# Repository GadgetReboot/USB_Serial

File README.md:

# USB_Serial
3.3v/5v CH340 USB to UART interface with all flow control and indicator signals broken out

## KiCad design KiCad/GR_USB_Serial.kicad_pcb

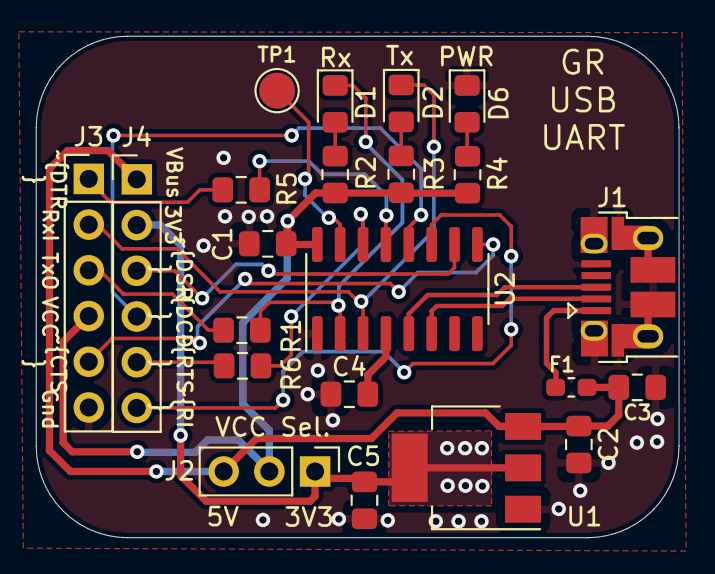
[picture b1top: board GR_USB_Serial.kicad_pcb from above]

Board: 2 copper layers, 35.7 x 27.9 mm, 22 parts (0 on the bottom side), 23 nets.

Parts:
C1, C2, C4: 100nF; C_0805_2012Metric_Pad1.15x1.40mm_HandSolder
C3: 1uF; C_0805_2012Metric_Pad1.15x1.40mm_HandSolder
C5: 4.7uF; C_0805_2012Metric_Pad1.15x1.40mm_HandSolder
D1: Rx; LED_0805_2012Metric_Pad1.15x1.40mm_HandSolder
D2: Tx; LED_0805_2012Metric_Pad1.15x1.40mm_HandSolder
D6: Power; LED_0805_2012Metric_Pad1.15x1.40mm_HandSolder
F1: MF-FSMF050X; R_0603_1608Metric_Pad1.05x0.95mm_HandSolder
J1: USB_B_Micro; USB_Micro-B_Amphenol_10103594-0001LF_Horizontal
J2: Conn_01x03; PinHeader_1x03_P2.54mm_Vertical
J3, J4: Conn_01x06; PinHeader_1x06_P2.54mm_Vertical
R1, R2, R3, R4, R5, R6: 1K; R_0805_2012Metric_Pad1.15x1.40mm_HandSolder
TP1: TestPoint; TestPoint_Pad_D2.0mm
U1: AMS1117-3.3; SOT-223-3_TabPin2
U2: CH340C; SOIC-16_3.9x9.9mm_P1.27mm

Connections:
+3V3: C5.1, J2.1, J4.2, U1.2
/RX_In: D2.1, J3.2, U2.3
/TX_Out: J3.3, R1.2
/~CTS: J3.5, U2.9
/~DCD: J4.4, U2.12
/~DSR: J4.3, U2.10
/~DTR: J3.1, R5.2
/~RI: J4.6, U2.11
/~RTS: J4.5, R6.2
GNDREF: C1.2, C2.2, C3.2, C4.2, C5.2, D6.1, J1.5, J1.6, J3.6, U1.1, U2.1
unnamed: C4.1, U2.4
unnamed: D1.1, R1.1, U2.2
unnamed: D1.2, R2.1
unnamed: D2.2, R3.1
unnamed: D6.2, R4.2
unnamed: F1.1, J1.1
unnamed: J1.2, U2.6
unnamed: J1.3, U2.5
unnamed: R5.1, U2.13
unnamed: R6.1, U2.14
unnamed: TP1.1, U2.15
VBUS: C2.1, C3.1, F1.2, J2.3, J4.1, U1.3
VCC: C1.1, J2.2, J3.4, R2.2, R3.2, R4.1, U2.16
